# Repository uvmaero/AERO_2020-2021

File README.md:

#AERO Boards for 2020 - 2021 school year

See AERO_KiCAD_Library for custom libraries

Each folder contains the board and firmware. This results in a large repo, but for our application seems like the best solution. This repo is set by the school year and each year boards change / adapt.

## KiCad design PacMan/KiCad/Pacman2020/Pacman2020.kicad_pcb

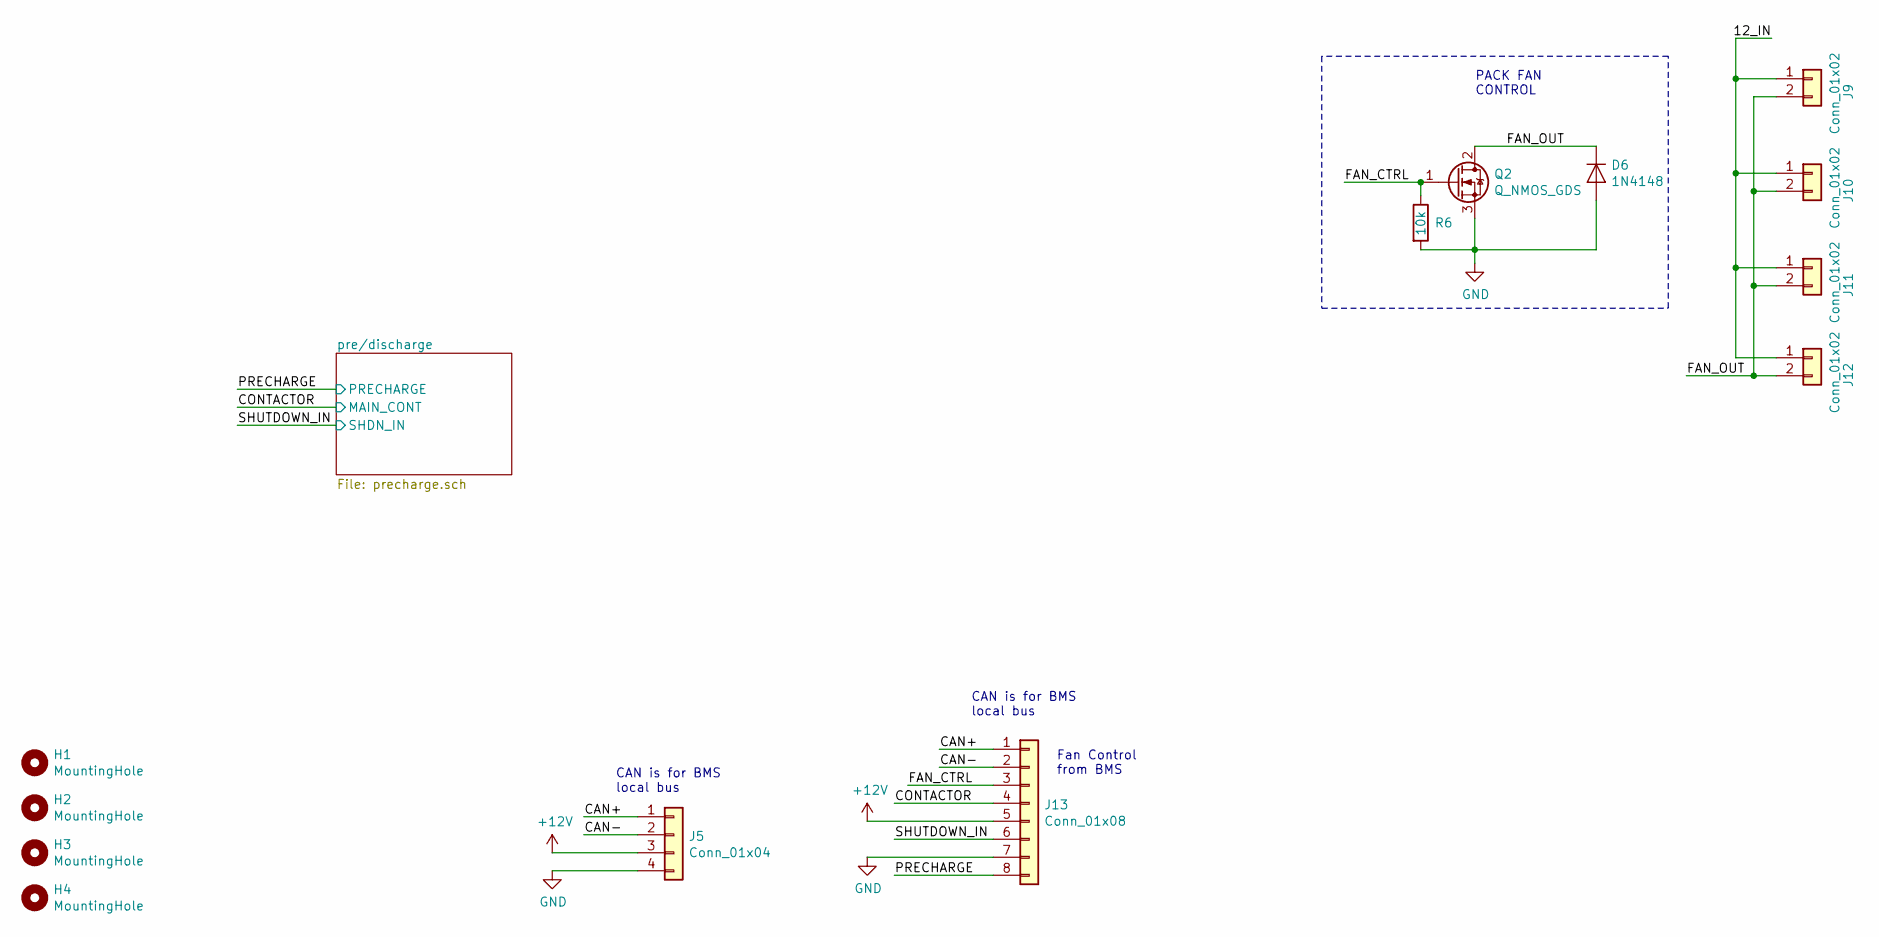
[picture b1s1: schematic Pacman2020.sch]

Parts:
D6: 1N4148; D_DO-35_SOD27_P7.62mm_Horizontal
H1, H2, H3, H4: MountingHole; MountingHole_3.2mm_M3
J5: Conn_01x04; JST_PH_B4B-PH-K_1x04_P2.00mm_Vertical
J9, J10, J11, J12: Conn_01x02; JST_VH_B2P-VH-B_1x02_P3.96mm_Vertical
J13: Conn_01x08; TE_1-776280-1_8pin_Horizontal
Q2: Q_NMOS_GDS; TO-252-3_TabPin2
R6: 10k; R_0603_1608Metric_Pad0.98x0.95mm_HandSolder

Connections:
+12V: J5.3, J13.5
/12_IN: J9.1, J10.1, J11.1, J12.1
/CAN+: J5.1, J13.1
/CAN-: J5.2, J13.2
/CONTACTOR: J13.4; also elsewhere on the board
/FAN_CTRL: J13.3, Q2.1 (G), R6.1
/FAN_OUT: D6.1 (K), J9.2, J10.2, J11.2, J12.2, Q2.2 (D)
/PRECHARGE: J13.8; also elsewhere on the board
/SHUTDOWN_IN: J13.6; also elsewhere on the board
GND: D6.2 (A), J5.4, J13.7, Q2.3 (S), R6.2; also elsewhere on the board

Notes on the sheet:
PACK FAN CONTROL
Fan Control from BMS
CAN is for BMS local bus

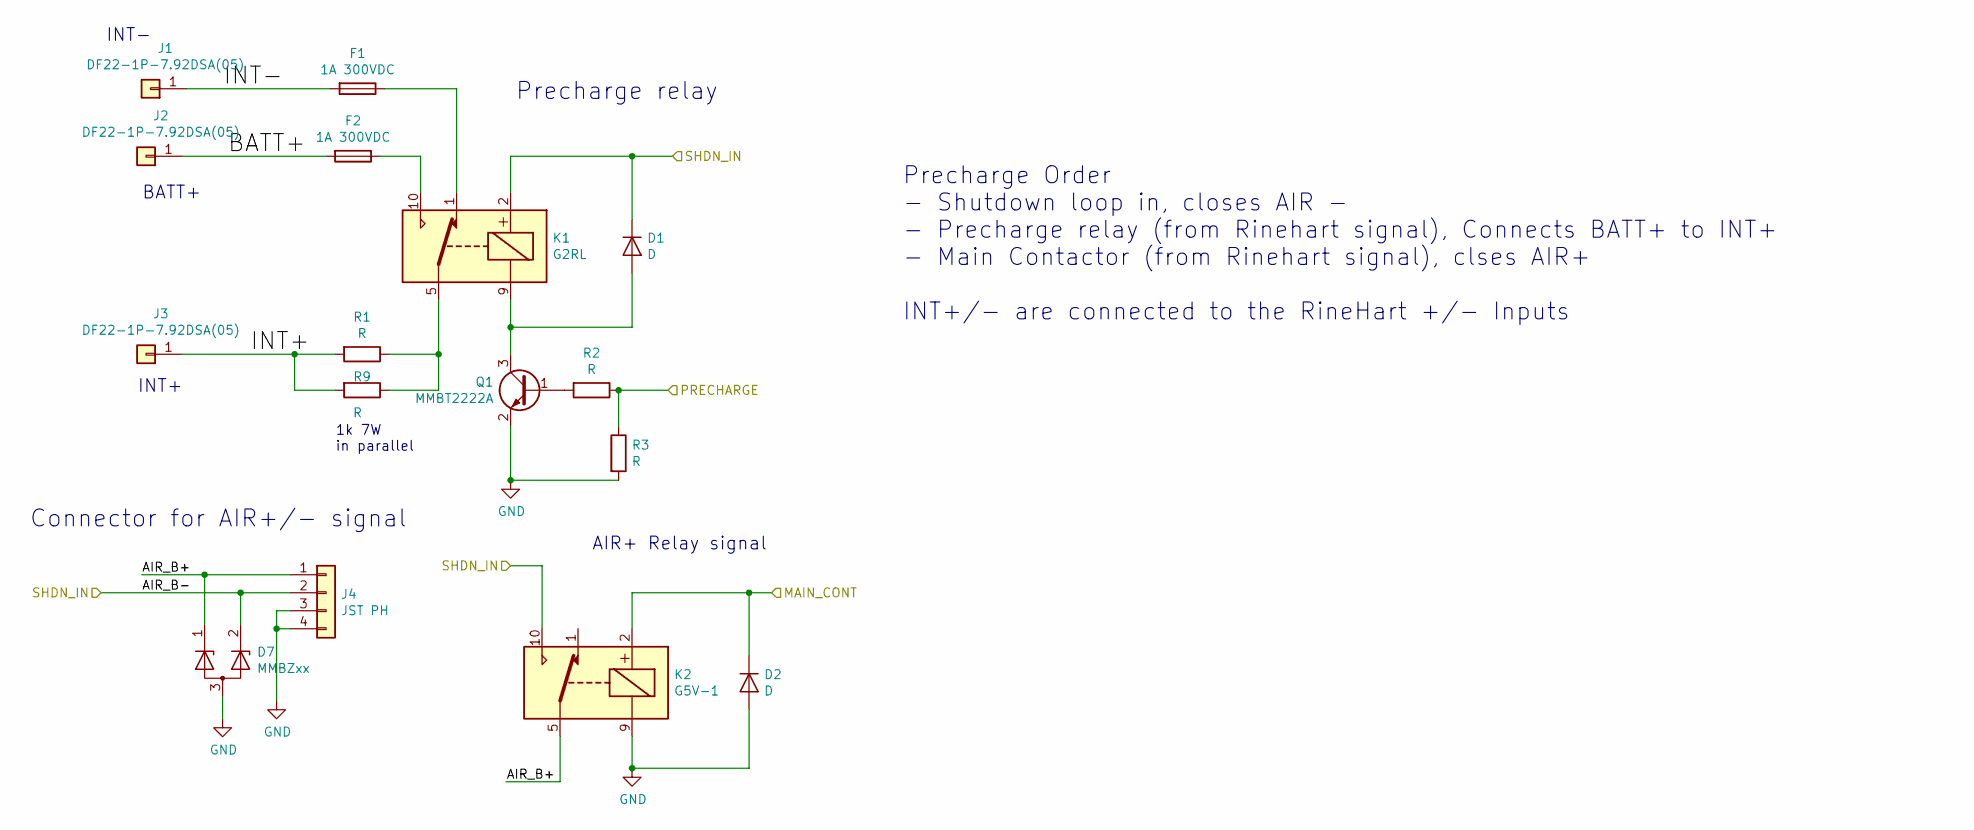
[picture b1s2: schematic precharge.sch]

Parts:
D1, D2: D; D_SOD-123
D7: MMBZxx; SOT-23
F1, F2: 1A 300VDC; Fuseholder_Cylinder-5x20mm_Schurter_0031_8201_Horizontal_Op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
J1, J2, J3: DF22-1P-7.92DSA(05); Hirose_DF63R-1P-3.96DSA_1x01_P3.96mm_Vertical
J4: JST PH; JST_PH_B4B-PH-K_1x04_P2.00mm_Vertical
K1: G2RL
K2: G5V-1; Relay_SPDT_Omron_G5V-1
Q1: MMBT2222A; SOT-23_Handsoldering
R1, R9: R; R_Axial_Power_L25.0mm_W9.0mm_P30.48mm
R2, R3: R; R_0603_1608Metric_Pad0.98x0.95mm_HandSolder

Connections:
/CONTACTOR: D2.1 (K), K2.2; also elsewhere on the board
/PRECHARGE: R2.1, R3.1; also elsewhere on the board
/SHUTDOWN_IN: D1.1 (K), D7.2 (K), J4.2, K1.2, K2.10; also elsewhere on the board
/pre/discharge/AIR_B+: D7.1 (K), J4.1, K2.5, K2.6
/pre/discharge/BATT+: F2.2, J2.1
/pre/discharge/INT+: J3.1, R1.2, R9.2
/pre/discharge/INT-: F1.2, J1.1
GND: D2.2 (A), D7.3 (A), J4.3, J4.4, K2.9, Q1.2 (E), R3.2; also elsewhere on the board
unnamed: D1.2 (A), K1.9, Q1.3 (C)
unnamed: F1.1, K1.1
unnamed: F2.1, K1.10
unnamed: K1.5, K1.6, R1.1, R9.1
unnamed: Q1.1 (B), R2.2

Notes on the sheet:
Precharge Order - Shutdown loop in, closes AIR - - Precharge relay (from Rinehart signal), Connects BATT+ to INT+ - Main Contactor (from Rinehart signal), clses AIR+ INT+/- are connected to the RineHart +/- Inputs
INT+
INT-
BATT+
AIR+ Relay signal
Precharge relay
Connector for AIR+/- signal
1k 7W in parallel

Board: 2 copper layers, 29 parts (2 on the bottom side), 19 nets, no tracks yet.

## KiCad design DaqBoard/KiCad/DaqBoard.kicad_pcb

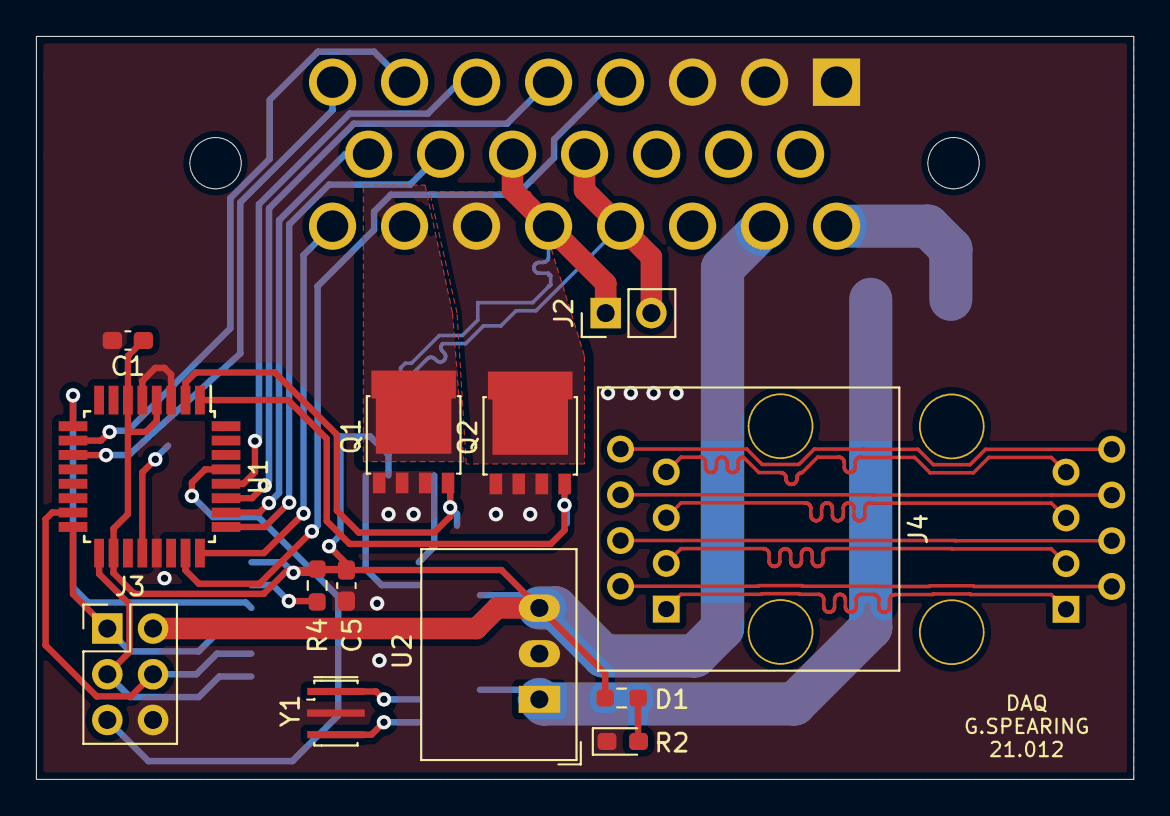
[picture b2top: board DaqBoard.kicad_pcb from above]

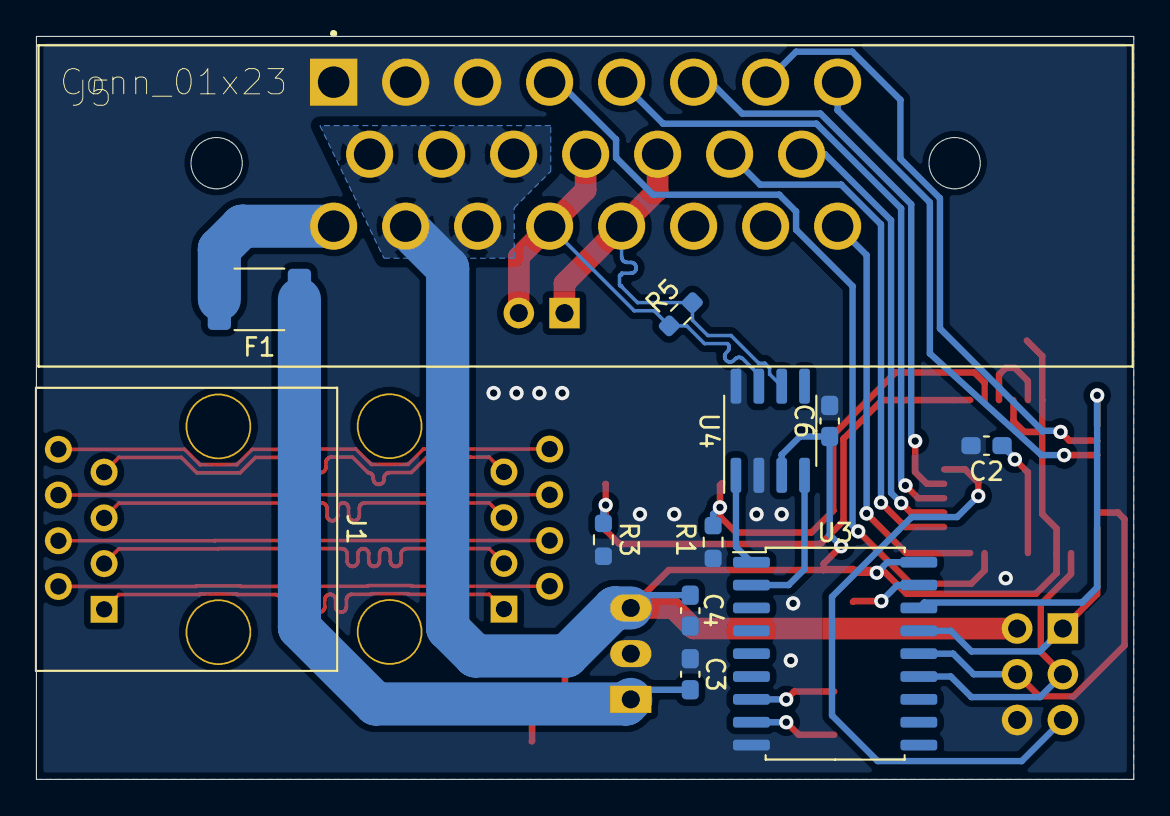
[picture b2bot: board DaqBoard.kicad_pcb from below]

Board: 2 copper layers, 61.0 x 41.3 mm, 25 parts (12 on the bottom side), 38 nets.

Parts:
C1, C2, C5, C6: 0.1u; C_0603_1608Metric_Pad1.08x0.95mm_HandSolder
C3: 1u; C_0603_1608Metric_Pad1.08x0.95mm_HandSolder
C4: 10u; C_0603_1608Metric_Pad1.08x0.95mm_HandSolder
D1: LED; LED_0603_1608Metric_Pad1.05x0.95mm_HandSolder
F1: MF-MSMF050; Fuse_1812_4532Metric_Pad1.30x3.40mm_HandSolder
J1, J4: RJ45; RJ45_TE_5569284-1-8P8CX_Vertical
J2: Conn_01x02; PinHeader_1x02_P2.54mm_Vertical
J3: Conn_02x03_Odd_Even; PinHeader_2x03_P2.54mm_Vertical
J5: Conn_01x23; TE_1-770669-1_23pin_Horizontal
Q1, Q2: PSMN5R2-60YL; LFPAK56
R1, R3, R4: 10K; R_0603_1608Metric_Pad0.98x0.95mm_HandSolder
R2: 330; R_0603_1608Metric_Pad0.98x0.95mm_HandSolder
R5: 120; R_0603_1608Metric_Pad0.98x0.95mm_HandSolder
U1: ATmega328P-AU; TQFP-32_7x7mm_P0.8mm
U2: R-785.0-1.0; Converter_DCDC_RECOM_R-78E-0.5_THT
U3: MCP2515-xSO; SOIC-18W_7.5x11.6mm_P1.27mm
U4: MCP2551-I-SN; SOIC-8_3.9x4.9mm_P1.27mm
Y1: 16MHz; Resonator_SMD_muRata_CSTxExxV-3Pin_3.0x1.1mm_HandSoldering

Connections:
+5V: C1.1, C4.1, C5.1, C6.1, J3.2, J5.9, J5.10, J5.11, J5.17, J5.18, R2.2, R4.1, U1.4, U1.6, U1.18, U2.3, U3.18, U4.3
+12V: F1.2, J5.16
/BRAKE_OUT: J5.22, Q1.5
/BRAKE_SIG: Q1.4, R1.1, U1.2
/CAN+: J2.2, J5.12, J5.19, R5.1, U4.7
/CAN-: J2.1, J5.13, J5.20, R5.2, U4.6
/CAN_CS: U1.9, U3.16
/CAN_Interface/RXCAN: U3.2, U4.4
/CAN_Interface/TXCAN: U3.1, U4.1
/DAMPER_L: J5.14, U1.25
/DAMPER_R: J5.15, U1.26
/E1_N: J1.2, J4.2
/E1_P: J1.1, J4.1
/E2_N: J1.4, J4.4
/E2_P: J1.3, J4.3
/E3_N: J1.6, J4.6
/E3_P: J1.5, J4.5
/E4_N: J1.8, J4.8
/E4_P: J1.7, J4.7
/FAN_OUT: J5.21, Q2.5
/FAN_SIG: Q2.4, R3.1, U1.1
/MISO: J3.1, U1.16, U3.15
/MOSI: J3.4, U1.15, U3.14
/RESET: J3.5, U1.29
/SCK: J3.3, U1.17, U3.13
/SENSOR_1: J5.7, U1.10
/SENSOR_2: J5.8, U1.11
/SENSOR_5: J5.5, U1.27
/SENSOR_6: J5.6, U1.28
/WHEEL_L: J5.4, U1.23
/WHEEL_R: J5.23, U1.24
GND: C1.2, C2.2, C3.2, C4.2, C5.2, C6.2, D1.1, J3.6, J5.1, J5.2, J5.3, Q1.1, Q1.2, Q1.3, Q2.1, Q2.2, Q2.3, R1.2, R3.2, U1.3, U1.5, U1.21, U2.2, U3.9, U4.2, U4.8, Y1.2
unnamed: C2.1, U1.20
unnamed: C3.1, F1.1, U2.1
unnamed: D1.2, R2.1
unnamed: R4.2, U3.17
unnamed: U3.7, Y1.1
unnamed: U3.8, Y1.3

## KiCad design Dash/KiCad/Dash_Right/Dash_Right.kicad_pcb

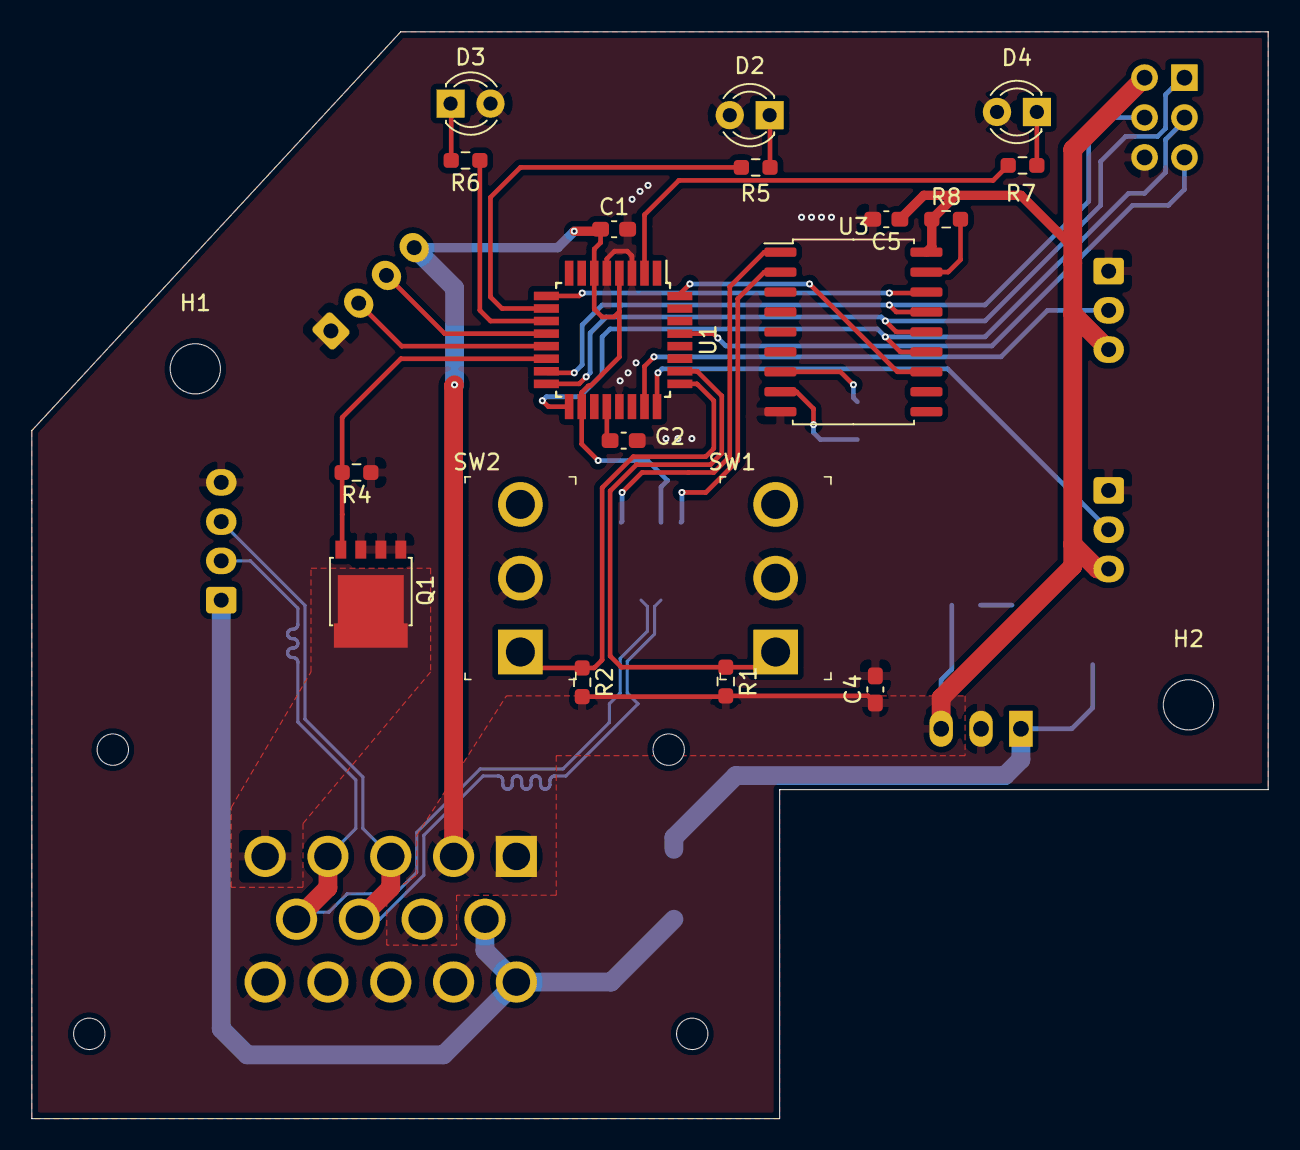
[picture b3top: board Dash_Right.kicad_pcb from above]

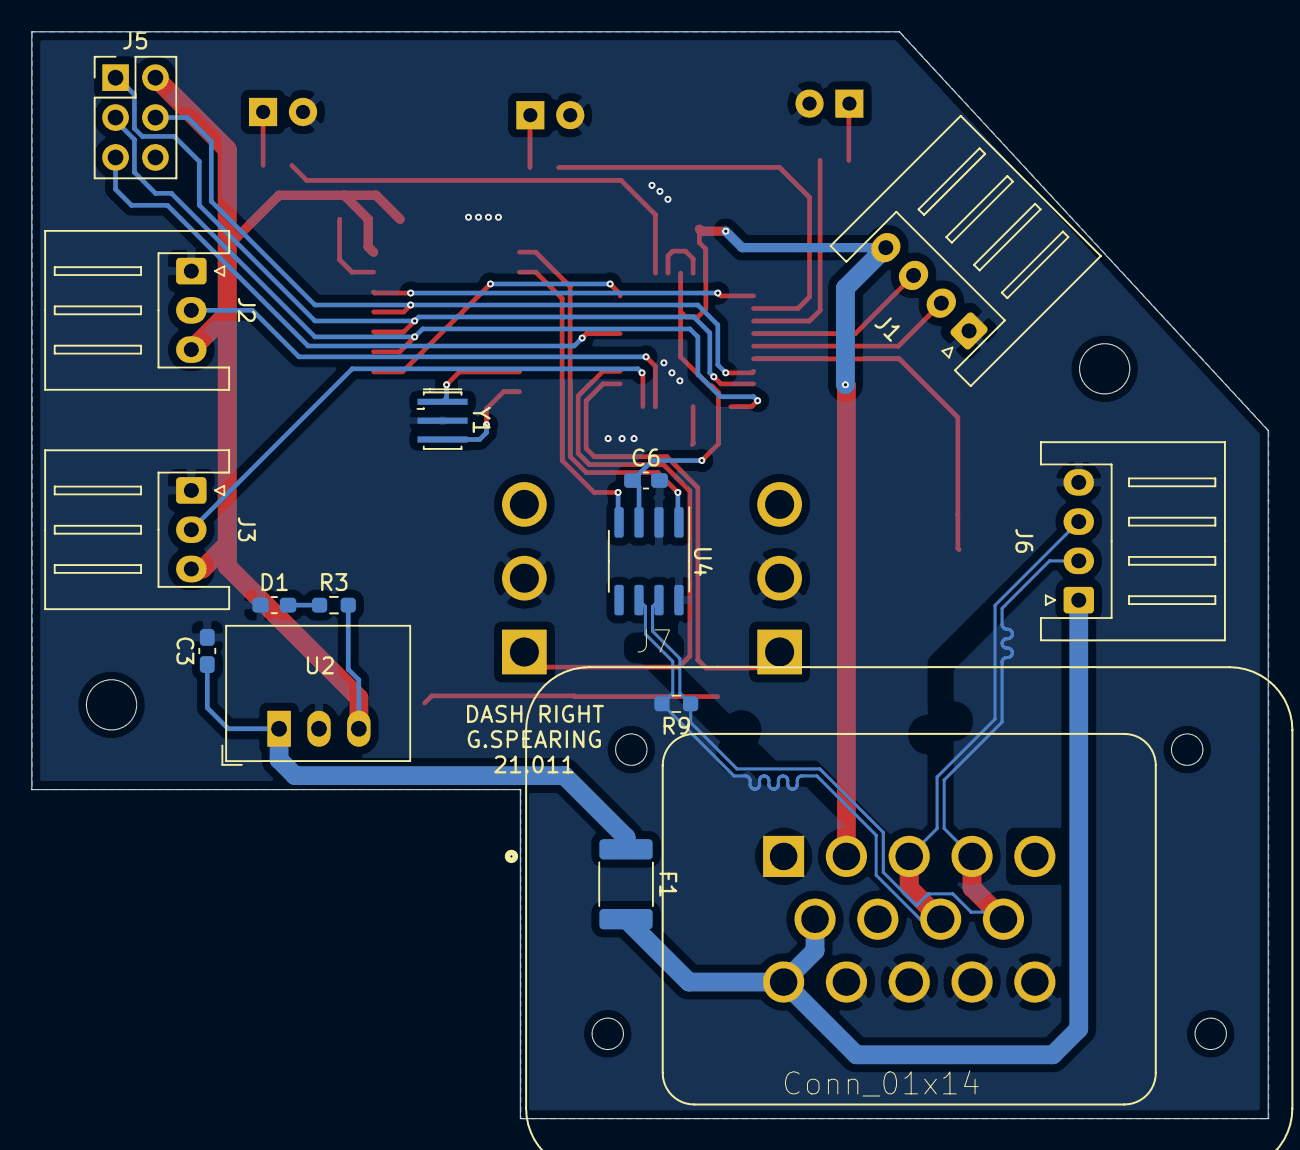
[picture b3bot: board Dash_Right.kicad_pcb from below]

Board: 2 copper layers, 78.7 x 69.2 mm, 36 parts (15 on the bottom side), 33 nets.

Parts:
C1, C2, C5, C6: 0.1u; C_0603_1608Metric_Pad1.08x0.95mm_HandSolder
C3: 1u; C_0603_1608Metric_Pad1.08x0.95mm_HandSolder
C4: 10u; C_0603_1608Metric_Pad1.08x0.95mm_HandSolder
D1: LED; Fuse_0603_1608Metric_Pad1.05x0.95mm_HandSolder
D2, D3, D4: LED; LED_D3.0mm
F1: MF-MSMF050; Fuse_1812_4532Metric_Pad1.30x3.40mm_HandSolder
H1, H2: MountingHole; MountingHole_3.2mm_M3
J1, J6: Conn_01x04; JST_XH_S4B-XH-A_1x04_P2.50mm_Horizontal
J2, J3: Conn_01x03; JST_XH_S3B-XH-A_1x03_P2.50mm_Horizontal
J5: Conn_02x03_Odd_Even; PinHeader_2x03_P2.54mm_Vertical
J7: Conn_01x14; TE_1-776262-1_14pin_Vertical
Q1: PSMN5R2-60YL; LFPAK56
R1, R2, R4, R8: 10K; R_0603_1608Metric_Pad0.98x0.95mm_HandSolder
R3, R5, R6, R7: 330; R_0603_1608Metric_Pad0.98x0.95mm_HandSolder
R9: 120; R_0603_1608Metric_Pad0.98x0.95mm_HandSolder
SW1, SW2: SW_SPDT; Toggle_Switch_100SP1T1B4M2QE
U1: ATmega328P-AU; TQFP-32_7x7mm_P0.8mm
U2: R-785.0-1.0; Converter_DCDC_RECOM_R-78E-0.5_THT
U3: MCP2515-xSO; SOIC-18W_7.5x11.6mm_P1.27mm
U4: MCP2551-I-SN; SOIC-8_3.9x4.9mm_P1.27mm
Y1: 16MHz; Resonator_SMD_muRata_CSTxExxV-3Pin_3.0x1.1mm_HandSoldering

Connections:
+5V: C1.1, C4.1, C5.1, C6.1, J1.4, J2.3, J3.3, J5.2, J7.1, J7.2, J7.7, R1.2, R2.2, R3.2, R8.1, U1.4, U1.6, U1.18, U2.3, U3.18, U4.3
+12V: F1.2, J6.1, J7.6, J7.10
/BMS_LED: R7.1, U1.2
/CAN+: J6.2, J7.4, J7.9, R9.1, U4.7
/CAN-: J6.3, J7.3, J7.8, R9.2, U4.6
/CAN_CS: U1.9, U3.16
/CAN_INT: U1.32, U3.12
/CAN_Interface/RXCAN: U3.2, U4.4
/CAN_Interface/TXCAN: U3.1, U4.1
/COAST: J2.2, U1.23
/COOLING: R1.1, SW1.1, U1.26
/DIRECTION: R2.1, SW2.1, U1.25
/IMD_LED: R5.1, U1.10
/MISO: J5.1, U1.16, U3.14
/MOSI: J5.4, U1.15, U3.15
/REGEN: J3.2, U1.24
/RESET: J5.5, U1.29
/RTD_BTN: J1.3, U1.12
/RTD_IND: Q1.4, R4.2, U1.14
/RTD_IND_OUT: J7.5, Q1.5
/RTD_LED: J1.2, U1.13
/SCK: J5.3, U1.17, U3.13
/TMS_LED: R6.1, U1.11
GND: C1.2, C2.2, C3.2, C4.2, C5.2, C6.2, D1.1, D2.2, D3.2, D4.2, J1.1, J2.1, J3.1, J5.6, J6.4, J7.11, J7.12, J7.13, J7.14, Q1.1, Q1.2, Q1.3, R4.1, SW1.2, SW2.2, U1.3, U1.5, U1.21, U2.2, U3.9, U4.2, U4.8, Y1.2
unnamed: C2.1, U1.20
unnamed: C3.1, F1.1, U2.1
unnamed: D1.2, R3.1
unnamed: D2.1, R5.2
unnamed: D3.1, R6.2
unnamed: D4.1, R7.2
unnamed: R8.2, U3.17
unnamed: U3.7, Y1.1
unnamed: U3.8, Y1.3

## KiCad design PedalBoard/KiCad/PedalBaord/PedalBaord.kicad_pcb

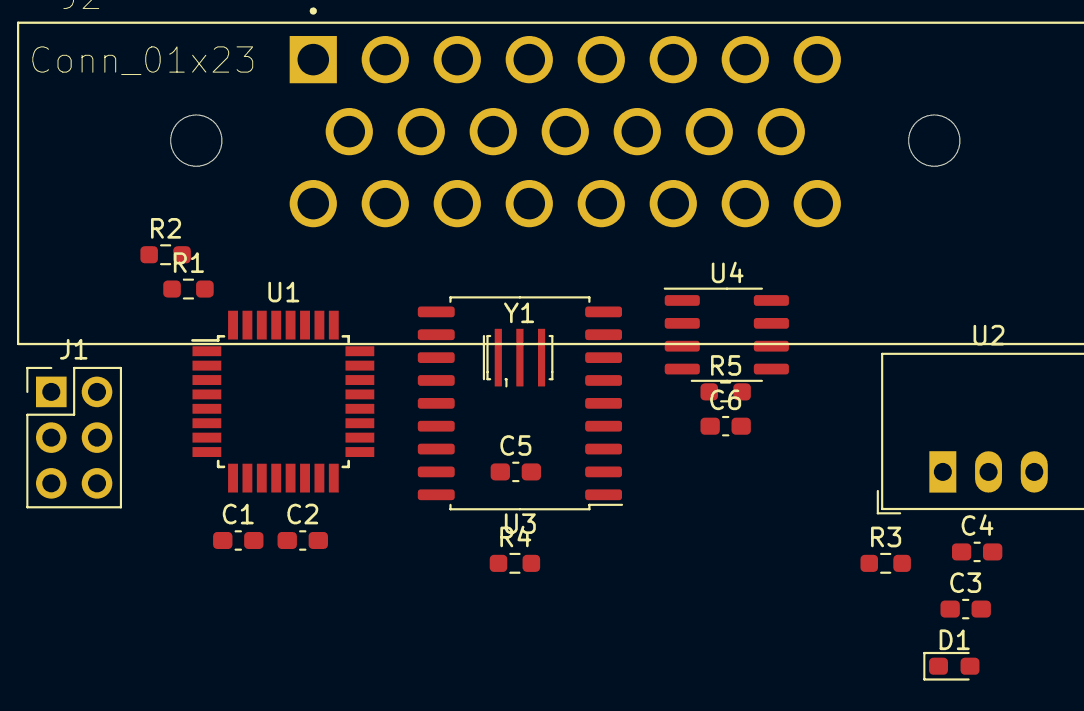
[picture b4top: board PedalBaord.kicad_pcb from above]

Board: 2 copper layers, 20 parts (1 on the bottom side), 28 nets, no tracks yet.

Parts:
C1, C2, C5, C6: 0.1u; C_0603_1608Metric_Pad1.08x0.95mm_HandSolder
C3: 1u; C_0603_1608Metric_Pad1.08x0.95mm_HandSolder
C4: 10u; C_0603_1608Metric_Pad1.08x0.95mm_HandSolder
D1: LED; LED_0603_1608Metric_Pad1.05x0.95mm_HandSolder
F1: MF-MSMF050; Fuse_1812_4532Metric_Pad1.30x3.40mm_HandSolder
J1: Conn_02x03_Odd_Even; PinHeader_2x03_P2.54mm_Vertical
J2: Conn_01x23; TE_1-770669-1_23pin_Horizontal
R1, R2, R4: 10K; R_0603_1608Metric_Pad0.98x0.95mm_HandSolder
R3: 330; R_0603_1608Metric_Pad0.98x0.95mm_HandSolder
R5: 120; R_0603_1608Metric_Pad0.98x0.95mm_HandSolder
U1: ATmega328P-AU; TQFP-32_7x7mm_P0.8mm
U2: R-785.0-1.0; Converter_DCDC_RECOM_R-78E-0.5_THT
U3: MCP2515-xSO; SOIC-18W_7.5x11.6mm_P1.27mm
U4: MCP2551-I-SN; SOIC-8_3.9x4.9mm_P1.27mm
Y1: 16MHz; Resonator_SMD_muRata_CSTxExxV-3Pin_3.0x1.1mm_HandSoldering

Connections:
+5V: C1.1, C4.1, C5.1, C6.1, J1.2, J2.12, J2.13, J2.14, J2.15, R3.2, R4.1, U1.4, U1.6, U1.18, U2.3, U3.18, U4.3
+12V: F1.2, J2.18, J2.19
/ACC0: J2.4, R2.1, U1.26
/ACC1: J2.5, R1.1, U1.27
/BRAKE0: J2.2, U1.24
/BRAKE1: J2.3, U1.25
/CANH: J2.7, J2.8, R5.1, U4.7
/CANL: J2.16, J2.17, R5.2, U4.6
/CAN_CS: U1.9, U3.16
/CAN_INT: U1.32, U3.12
/MISO: J1.1, U1.16, U3.15
/MOSI: J1.4, U1.15, U3.14
/RESET: J1.5, U1.29
/RXCAN: U3.2, U4.4
/SCK: J1.3, U1.17, U3.13
/SENSOR_1: J2.6, U1.1
/SENSOR_2: J2.9, U1.2
/SENSOR_3: J2.10, U1.10
/SENSOR_4: J2.11, U1.11
/STEER: J2.1, U1.23
/TXCAN: U3.1, U4.1
GND: C1.2, C2.2, C3.2, C4.2, C5.2, C6.2, D1.1, J1.6, J2.20, J2.21, J2.22, J2.23, R1.2, R2.2, U1.3, U1.5, U1.21, U2.2, U3.9, U4.2, U4.8, Y1.2
unnamed: C2.1, U1.20
unnamed: C3.1, F1.1, U2.1
unnamed: D1.2, R3.1
unnamed: R4.2, U3.17
unnamed: U3.7, Y1.1
unnamed: U3.8, Y1.3

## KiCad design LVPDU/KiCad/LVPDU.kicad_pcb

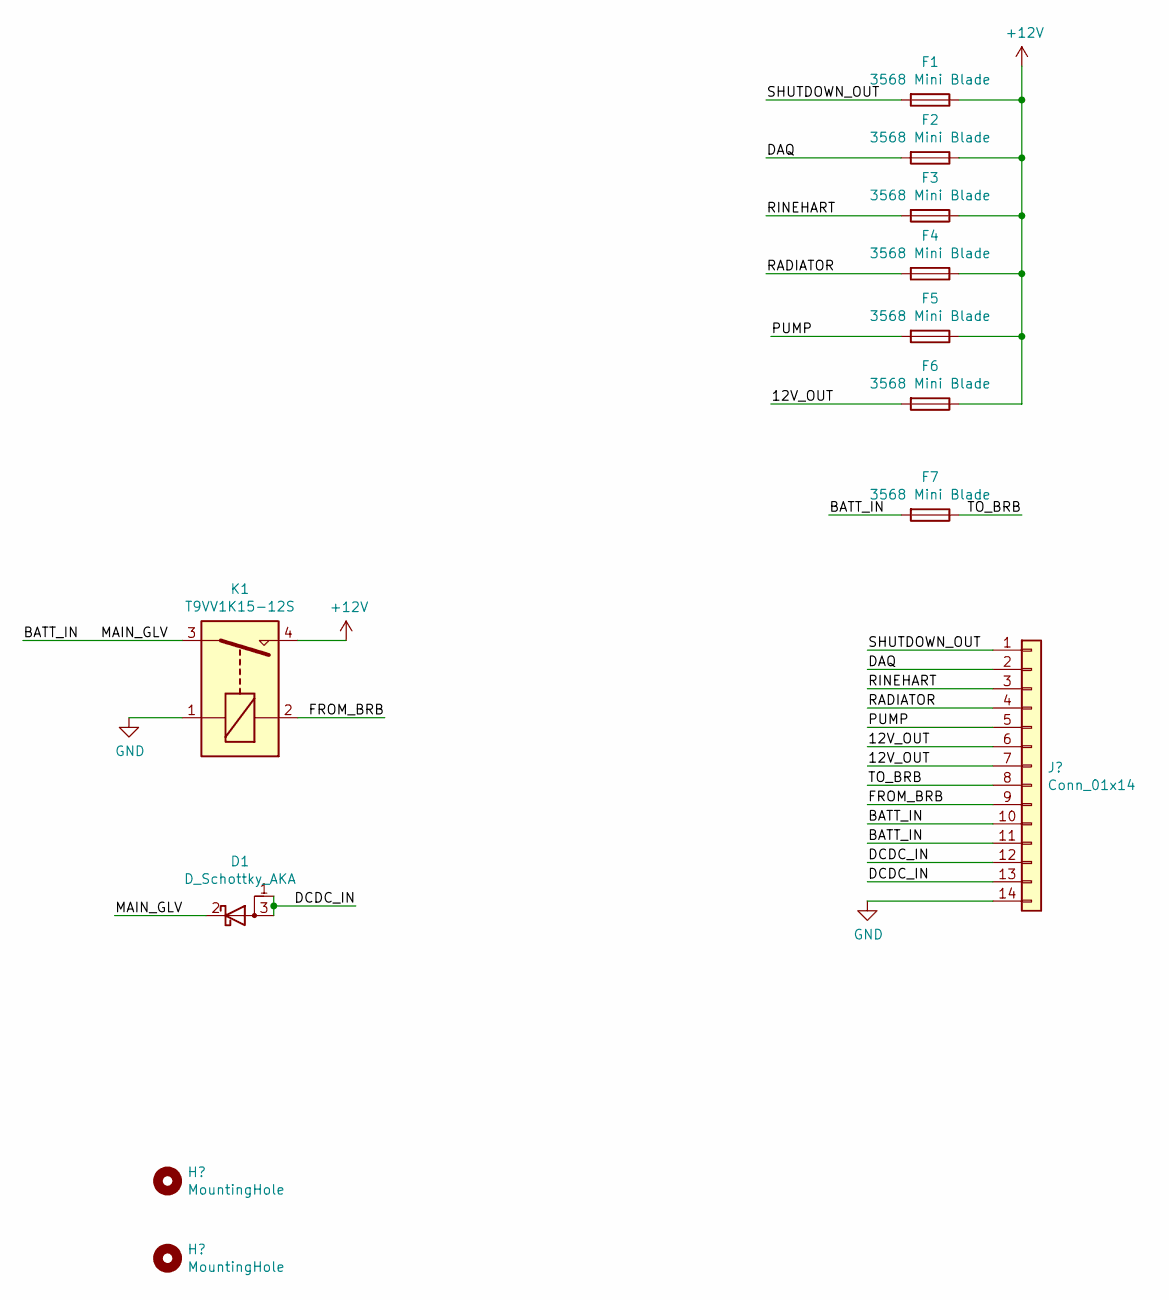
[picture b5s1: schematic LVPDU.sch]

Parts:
D1: D_Schottky_AKA
F1, F2, F3, F4, F5, F6, F7: 3568 Mini Blade
K1: T9VV1K15-12S; RELAY_T9VV1K15-12S

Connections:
+12V: F1.1, F2.1, F3.1, F4.1, F5.1, F6.1, K1.4
/12V_OUT: F6.2; also elsewhere on the board
/BATT_IN: D1.2 (K), F7.2, K1.3; also elsewhere on the board
/DAQ: F2.2; also elsewhere on the board
/DCDC_IN: D1.1 (A), D1.3 (A); also elsewhere on the board
/FROM_BRB: K1.2; also elsewhere on the board
/PUMP: F5.2; also elsewhere on the board
/RADIATOR: F4.2; also elsewhere on the board
/RINEHART: F3.2; also elsewhere on the board
/SHUTDOWN_OUT: F1.2; also elsewhere on the board
/TO_BRB: F7.1; also elsewhere on the board
GND: K1.1; also elsewhere on the board

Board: 2 copper layers, 12 parts (0 on the bottom side), 12 nets, no tracks yet.

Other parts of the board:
H1, H2: MountingHole; MountingHole_3.2mm_M3
J1: Conn_01x14; TE_1-776266-1_14pin_Horizontal

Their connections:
/12V_OUT: J1.6, J1.7; also elsewhere on the board
/BATT_IN: J1.10, J1.11; also elsewhere on the board
/DAQ: J1.2; also elsewhere on the board
/DCDC_IN: J1.12, J1.13; also elsewhere on the board
/FROM_BRB: J1.9; also elsewhere on the board
/PUMP: J1.5; also elsewhere on the board
/RADIATOR: J1.4; also elsewhere on the board
/RINEHART: J1.3; also elsewhere on the board
/SHUTDOWN_OUT: J1.1; also elsewhere on the board
/TO_BRB: J1.8; also elsewhere on the board
GND: J1.14; also elsewhere on the board

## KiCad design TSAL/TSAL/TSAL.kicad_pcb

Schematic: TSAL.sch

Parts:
C1: 0.1u; C_0603_1608Metric_Pad1.05x0.95mm_HandSolder
C2: 1u; C_0603_1608Metric_Pad1.05x0.95mm_HandSolder
H1: M3; MountingHole_3.2mm_M3
J1: Conn_01x02; Hirose_DF63R-2P-3.96DSA_1x02_P3.96mm_Vertical
J2, J3: 172165-1; TE_MATE-N-LOK_1-770866-x_1x02_P4.14mm_Vertical
Q1, Q2: 040N03LG; TO-252-3_TabPin2
R1: 39k; R_Axial_DIN0617_L17.0mm_D6.0mm_P30.48mm_Horizontal
R2, R5: 10k; R_0603_1608Metric_Pad1.05x0.95mm_HandSolder
R3: 100k; R_0603_1608Metric_Pad1.05x0.95mm_HandSolder
R4: 235k; R_0603_1608Metric_Pad1.05x0.95mm_HandSolder
R6: 0.75; R_2512_6332Metric_Pad1.52x3.35mm_HandSolder
U1: LTV-817S; SMDIP-4_W9.53mm
U2: LM555xM; SOIC-8_3.9x4.9mm_P1.27mm

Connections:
+12V: J2.1, J3.2, U1.4
/555_OUT: R5.2, U2.3 (Q)
/HV+: J1.2, R1.2
/HV-: J1.1, U1.2
/RED_ON: J3.1, Q2.2 (D)
/pass: C2.1, R4.2, U2.2 (TR), U2.6 (THR)
GND: C1.2, C2.2, J2.2, Q1.3 (S), R2.2, R6.1, U2.1 (GND)
unnamed: C1.1, U2.5 (CV)
unnamed: Q1.1 (G), Q2.3 (S), R6.2
unnamed: Q1.2 (D), Q2.1 (G), R5.1
unnamed: R1.1, U1.1
unnamed: R3.2, R4.1, U2.7 (DIS)
VCC: R2.1, R3.1, U1.3, U2.4 (R), U2.8 (VCC)

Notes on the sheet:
High Voltage
GLV
M3 Mounting Hole
CC Output
Change R6 for Current Rating
LED Connector

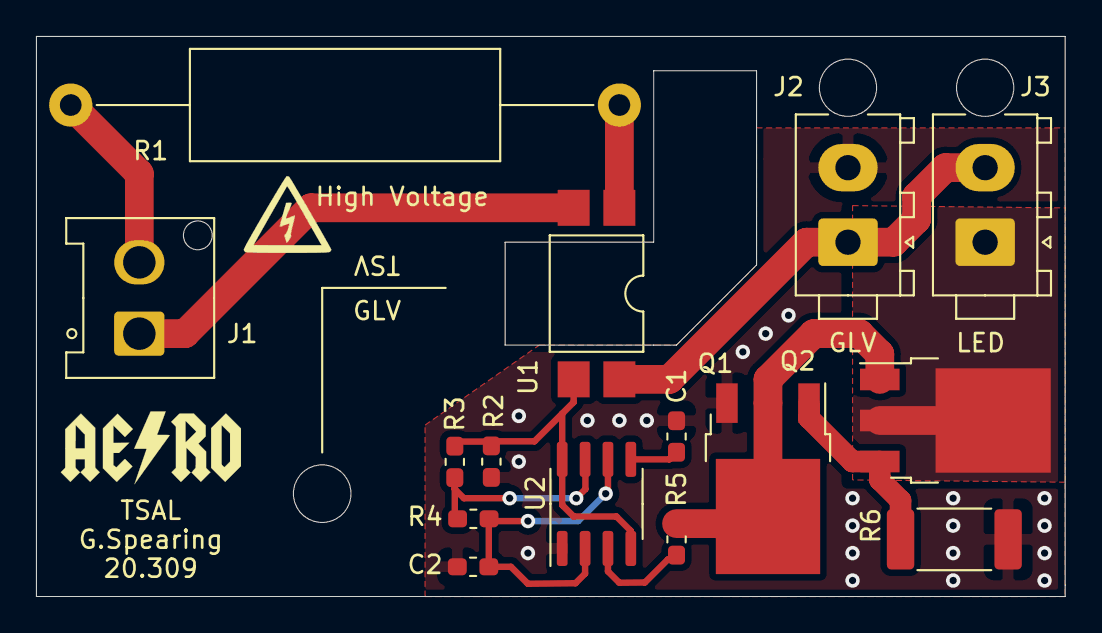
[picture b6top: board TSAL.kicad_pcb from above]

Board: 2 copper layers, 57.1 x 31.1 mm, 17 parts (0 on the bottom side), 13 nets.

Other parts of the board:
Ref**: Val**; hv_small

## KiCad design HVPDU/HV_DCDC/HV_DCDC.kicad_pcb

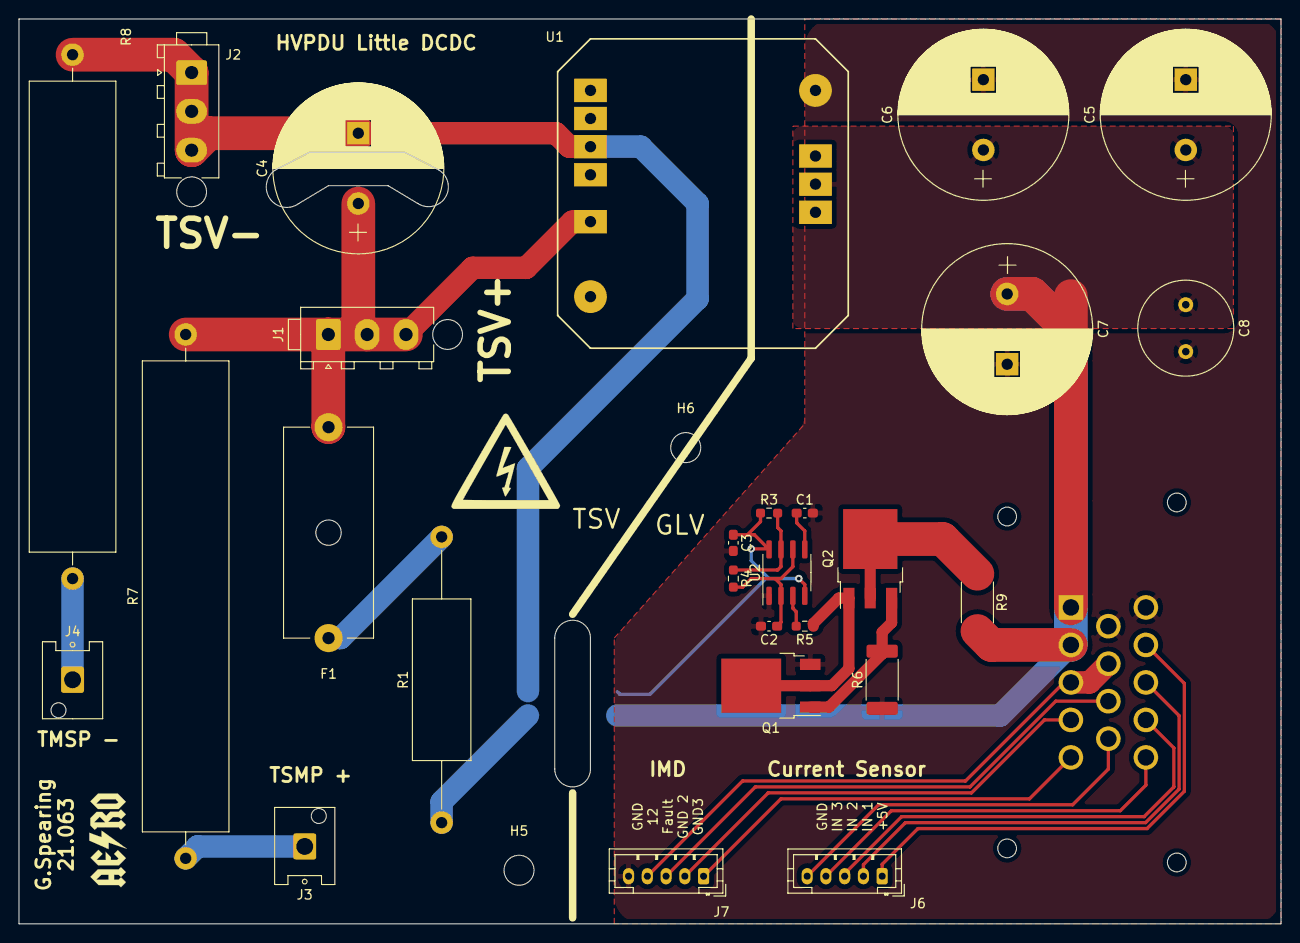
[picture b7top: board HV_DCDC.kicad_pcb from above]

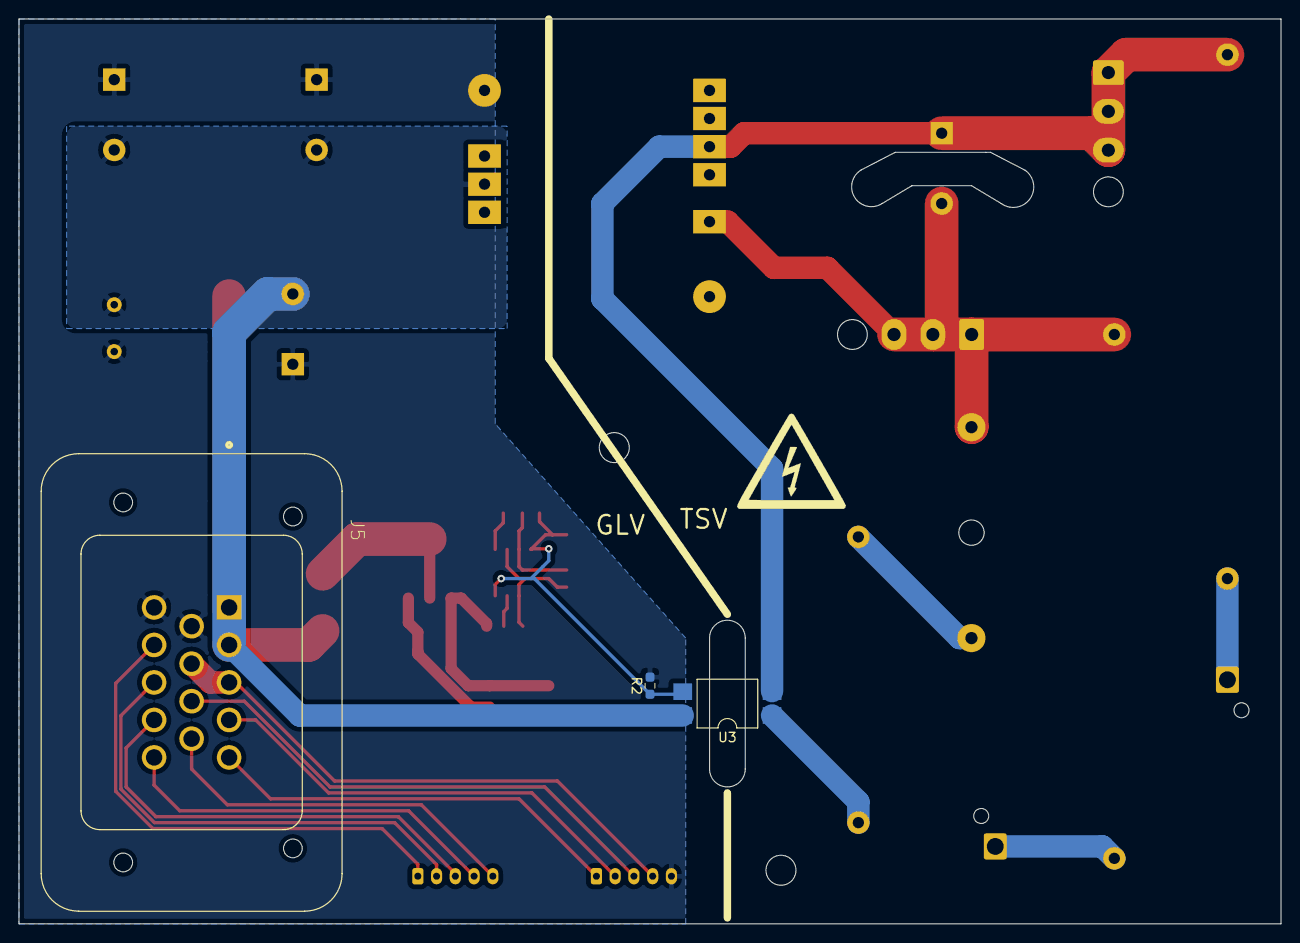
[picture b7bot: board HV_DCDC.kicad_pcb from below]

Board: 2 copper layers, 134.6 x 96.5 mm, 34 parts (4 on the bottom side), 26 nets.

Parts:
C1, C3: 0.1u; C_0603_1608Metric_Pad1.08x0.95mm_HandSolder
C2: 1u; C_0603_1608Metric_Pad1.08x0.95mm_HandSolder
C4: 33uF 450V; CAP_18x25_NICH
C5, C6: 330uF 25V; CAP_18x25_NICH
C7: 47uF 25V; CAP_18x25_NICH
C8: 0.1uF 50V; C_Radial_D10.0mm_H12.5mm_P5.00mm
F1: 0ADK-2.5A; Fuseholder_Cylinder-5x20mm_Schurter_0031_8201_Horizontal_Op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
H5, H6: M3; MountingHole_3.2mm_M3
J1, J2: TE_Connector; TE_MATE-N-LOK_1-770870-x_1x03_P4.14mm_Vertical
J3, J4: DF22; Hirose_DF63M-1P-3.96DSA_1x01_P3.96mm_Vertical
J5: Conn_01x14; TE_1-776262-1_14pin_Vertical
J6, J7: Conn_01x05; JST_PH_B5B-PH-K_1x05_P2.00mm_Vertical
Q1, Q2: 040N03LG; TO-252-3_TabPin2
R1: 39k; R_Axial_DIN0617_L17.0mm_D6.0mm_P30.48mm_Horizontal
R2, R5: 10k; R_0603_1608Metric_Pad0.98x0.95mm_HandSolder
R3: 100k; R_0603_1608Metric_Pad0.98x0.95mm_HandSolder
R4: 235k; R_0603_1608Metric_Pad0.98x0.95mm_HandSolder
R6: 0.75; R_2512_6332Metric_Pad1.40x3.35mm_HandSolder
R7, R8: 10k; R_Axial_Power_L50.0mm_W9.0mm_P55.88mm
R9: 1.0; R_2512_6332Metric_Pad1.40x3.35mm_HandSolder
Ref**: Val**; hv_big
Ref**#2: Val**; hv_big
U1: EPM1510SJ
U2: LM555; SOIC-8_3.9x4.9mm_P1.27mm
U3: LTV-817S; SMDIP-4_W9.53mm

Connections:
+5V: J5.11, J6.1
+12V: J5.3, J5.7, J7.4
/+DCDC_OUT: C5.1, C6.1, C7.1, C8.1, J5.1, U1.5, U3.4
/Fault_IND: J5.8, J7.3
/GND_Chassis: J5.4, J7.2
/GND_Electric: J5.5, J7.1
/INPUT1: J5.12, J6.2
/INPUT2: J5.13, J6.3
/INPUT3: J5.14, J6.4
/RED_ON_GND: J5.2, R9.2
/TSAL_TSV+: F1.1, R1.2
/TSAL_on_HVPDU/555_OUT: R5.2, U2.3
/TSAL_on_HVPDU/pass: C2.1, R4.2, U2.2, U2.6
/TSV+: C4.1, F1.2, J1.1, J1.2, J1.3, R7.2, U1.12
/TSV+_TSMP: J3.1, R7.1
/TSV-: C4.2, J2.1, J2.2, J2.3, R8.2, U1.10, U3.2
/TSV-_TSMP: J4.1, R8.1
GND: C1.2, C2.2, C3.2, C5.2, C6.2, C7.2, C8.2, J5.6, J5.10, J7.5, Q1.3, R2.2, R6.1, U1.7, U2.1
GNDREF: J5.9, J6.5
unnamed: C1.1, U2.5
unnamed: Q1.1, Q2.3, R6.2
unnamed: Q1.2, Q2.1, R5.1
unnamed: Q2.2, R9.1
unnamed: R1.1, U3.1
unnamed: R3.2, R4.1, U2.7
VCC: C3.1, R2.1, R3.1, U2.4, U2.8, U3.3

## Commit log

2020-07-07 ReadMe
2020-10-27 Schmatics and TSAL Inital
2020-10-30 finished TSAL rev1
2020-11-04 change to CC driver
2020-11-04 Packman Initial Commit
2021-01-10 pedal Board Schematic
2021-01-10 TSAL Schematic and layout
2021-01-10 Fault Latcher Schematic
2021-01-10 KiCad starting Schematic ATMEGA
2021-01-10 schematic and layout
2021-01-10 left and right dash schematic
2021-01-10 daq board schematic
2021-01-10 update can interface defaults
2021-01-10 update schematic
2021-01-10 LVPDU schematic
2021-01-10 what happened?
2021-01-10 add interface hierarchy
2021-01-11 emrax breakout board
2021-01-11 daq board firmware
2021-01-11 daq board description update
2021-01-11 pedalboard initial firmware commit
2021-01-11 Fault Latcher Firmware Init
2021-01-11 Dash Right first commit
2021-01-11 change folder name
2021-01-11 Dash Left firmware first commit
2021-01-12 initial pcb layout
2021-01-12 Inital pcb layout
2021-01-12 inital layouts
2021-01-13 first layout design
2021-01-14 update PCB Layout
2021-01-14 Fault Latcher Code Creation
2021-01-14 minor layout update
2021-01-17 update daq time before interrupts
2021-01-17 Variable Delcarations, Some Functions
2021-01-17 add can setup
2021-01-18 update start button pin
2021-01-18 Major updates, CAN Handling, Interfacing
2021-01-18 Minor updates in comments
2021-01-20 Minor Function Updates and ToDo Lists
2021-01-20 PacMan initial commit
2021-01-20 Minor updates
2021-01-21 update file names
2021-01-21 Change to two switch config
2021-01-21 Change file location
2021-01-22 Add precharge documentation
2021-01-23 60V indicator initial commit
2021-02-10 first board rev
2021-02-10 added documentaiton
2021-02-10 layout changes
2021-02-10 pinout updates / timing
2021-02-17 add contact note
2021-02-18 HV Board Initial upload
2021-02-18 minor update thing
2021-02-19 notes from design review 1
2021-02-19 add note
2021-02-19 please work
2021-02-19 remove ATMEGA, add BMS fan control
2021-02-19 good symbols now
2021-02-19 I didn't actually change anything
2021-03-05 Make new small DCDC and HVPDU board
2021-03-05 gerber files
2021-03-05 update HVPDU board with TSAL integration
2021-03-05 rescue files
2021-03-05 minor stuffs
2021-03-05 update vicor settings stuffs
2021-03-08 start layout
2021-03-12 Initial Wiring Harness
    Started document, but blank. Moved to RapidHarness
2021-03-12 Add Fuse Ratings
2021-03-17 Change HV PCB Layout
2021-03-18 update layout, finalize
2021-03-18 create gerber
2021-03-18 update schematic and layout
